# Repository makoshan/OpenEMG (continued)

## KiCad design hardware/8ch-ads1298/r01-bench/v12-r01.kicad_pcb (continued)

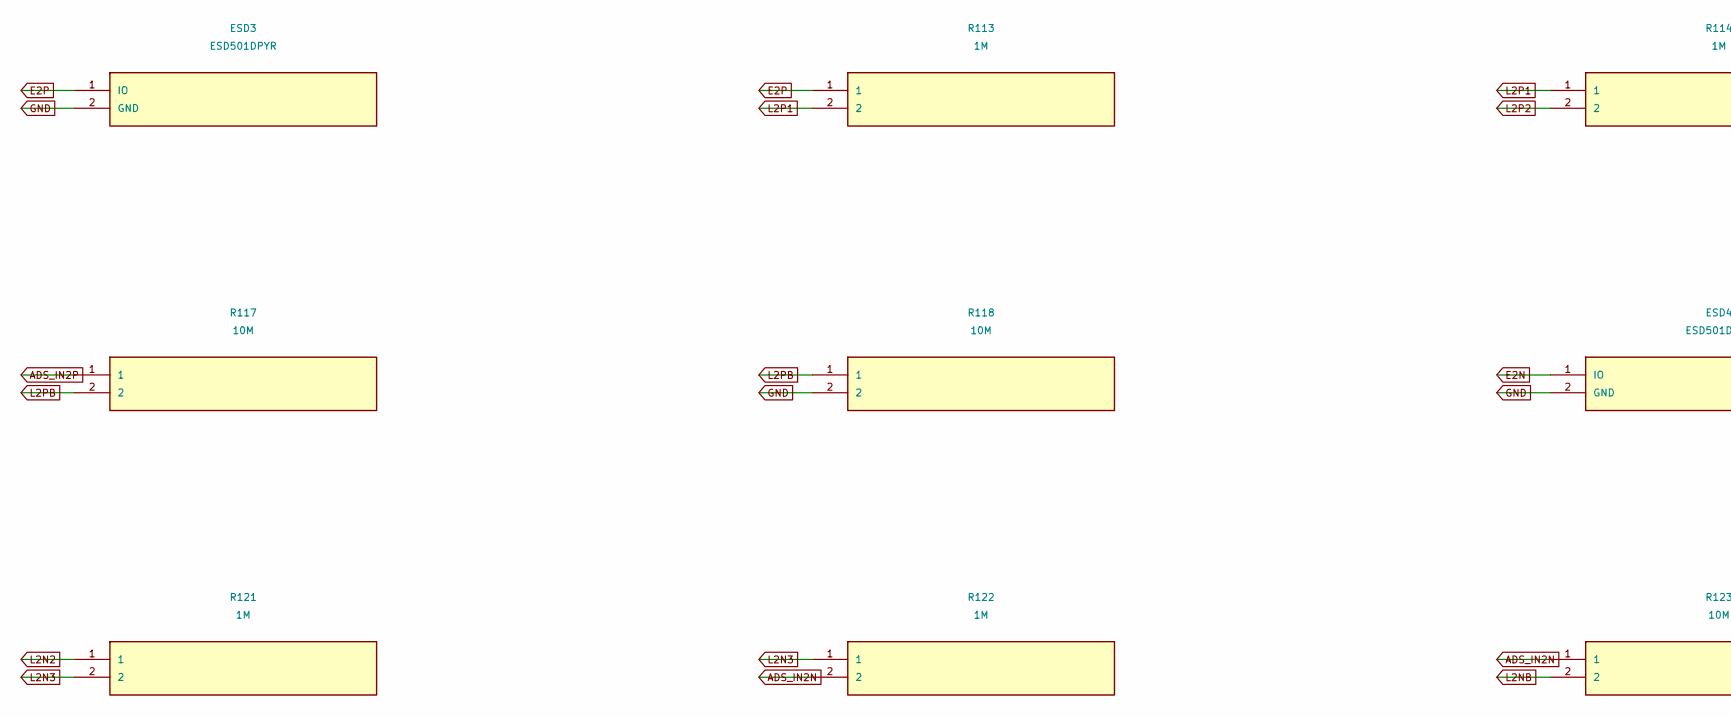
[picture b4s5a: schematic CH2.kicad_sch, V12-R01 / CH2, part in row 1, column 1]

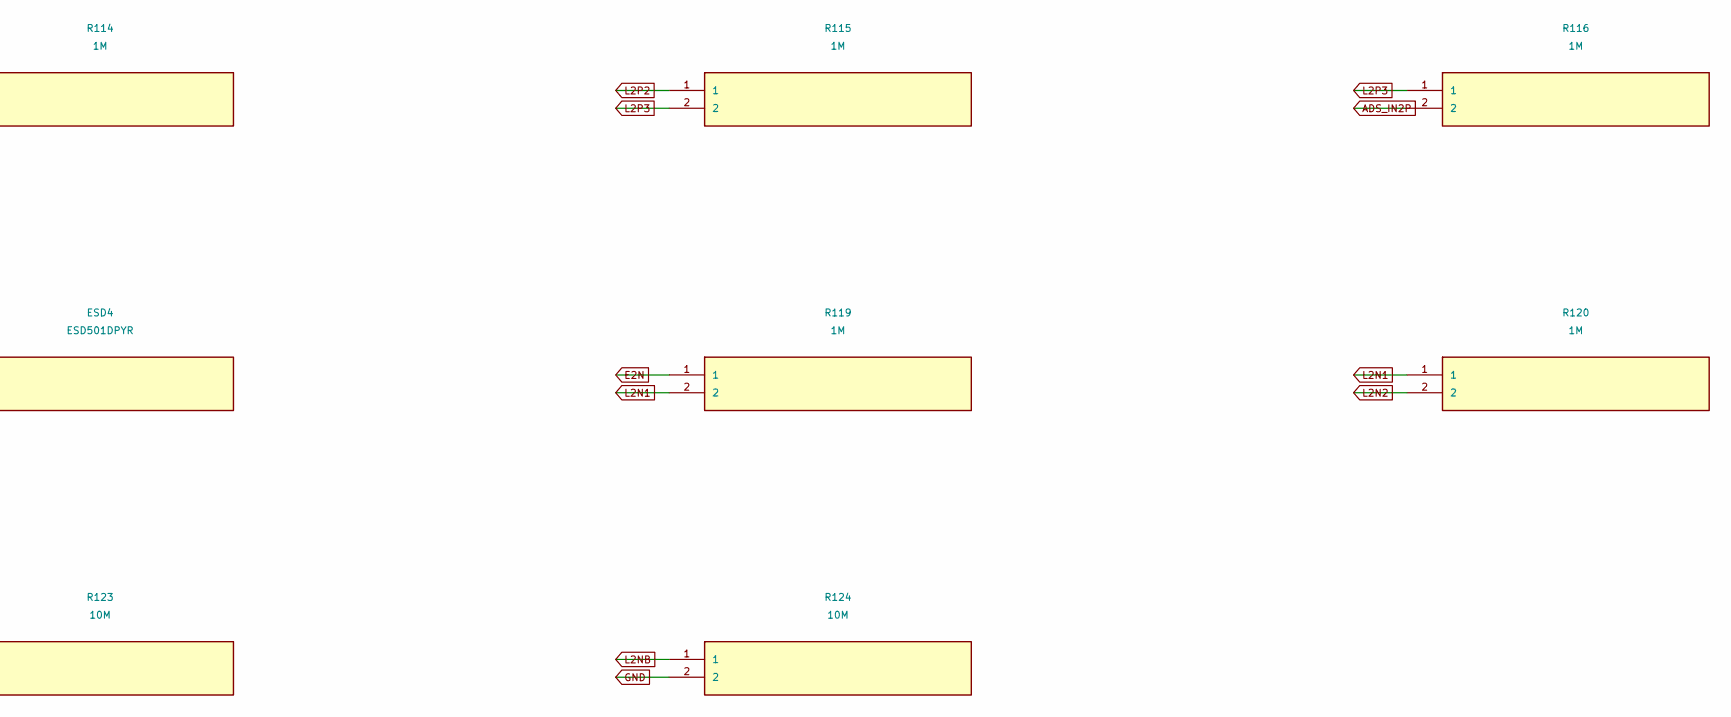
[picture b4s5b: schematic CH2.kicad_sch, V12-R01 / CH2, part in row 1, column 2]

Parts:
ESD3, ESD4: ESD501DPYR; Texas_DPY0002A_0.6x1mm_P0.65mm
R113, R114, R115, R116, R119, R120, R121, R122: 1M; R_0402_1005Metric
R117, R118, R123, R124: 10M; R_0402_1005Metric

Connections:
ADS_IN2N: R122.2, R123.1; also elsewhere on the board
ADS_IN2P: R116.2, R117.1; also elsewhere on the board
E2N: ESD4.1 (IO), R119.1; also elsewhere on the board
E2P: ESD3.1 (IO), R113.1; also elsewhere on the board
GND: ESD3.2 (GND), ESD4.2 (GND), R118.2, R124.2; also elsewhere on the board
L2N1: R119.2, R120.1
L2N2: R120.2, R121.1
L2N3: R121.2, R122.1
L2NB: R123.2, R124.1
L2P1: R113.2, R114.1
L2P2: R114.2, R115.1
L2P3: R115.2, R116.1
L2PB: R117.2, R118.1

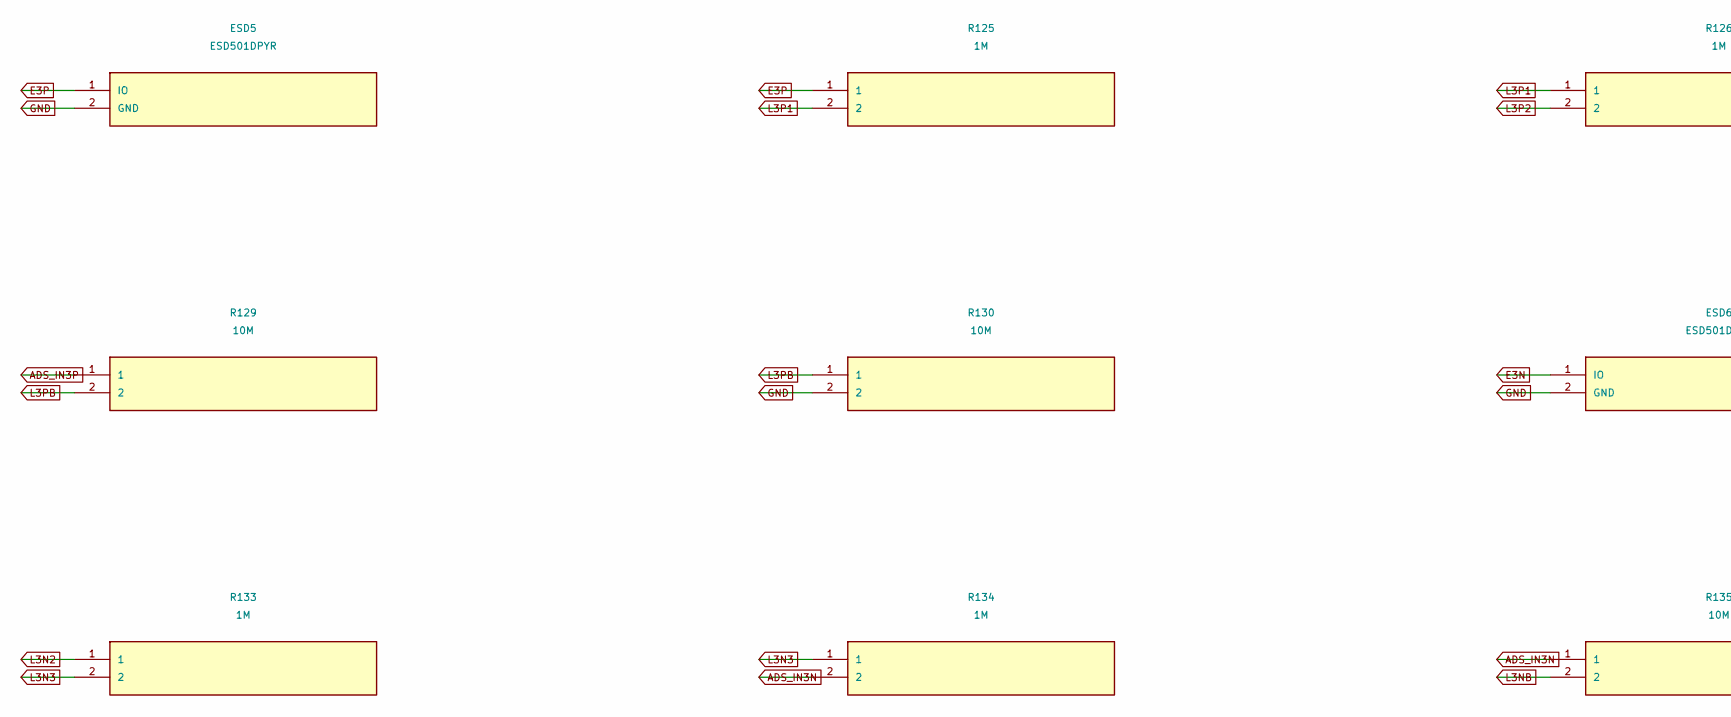
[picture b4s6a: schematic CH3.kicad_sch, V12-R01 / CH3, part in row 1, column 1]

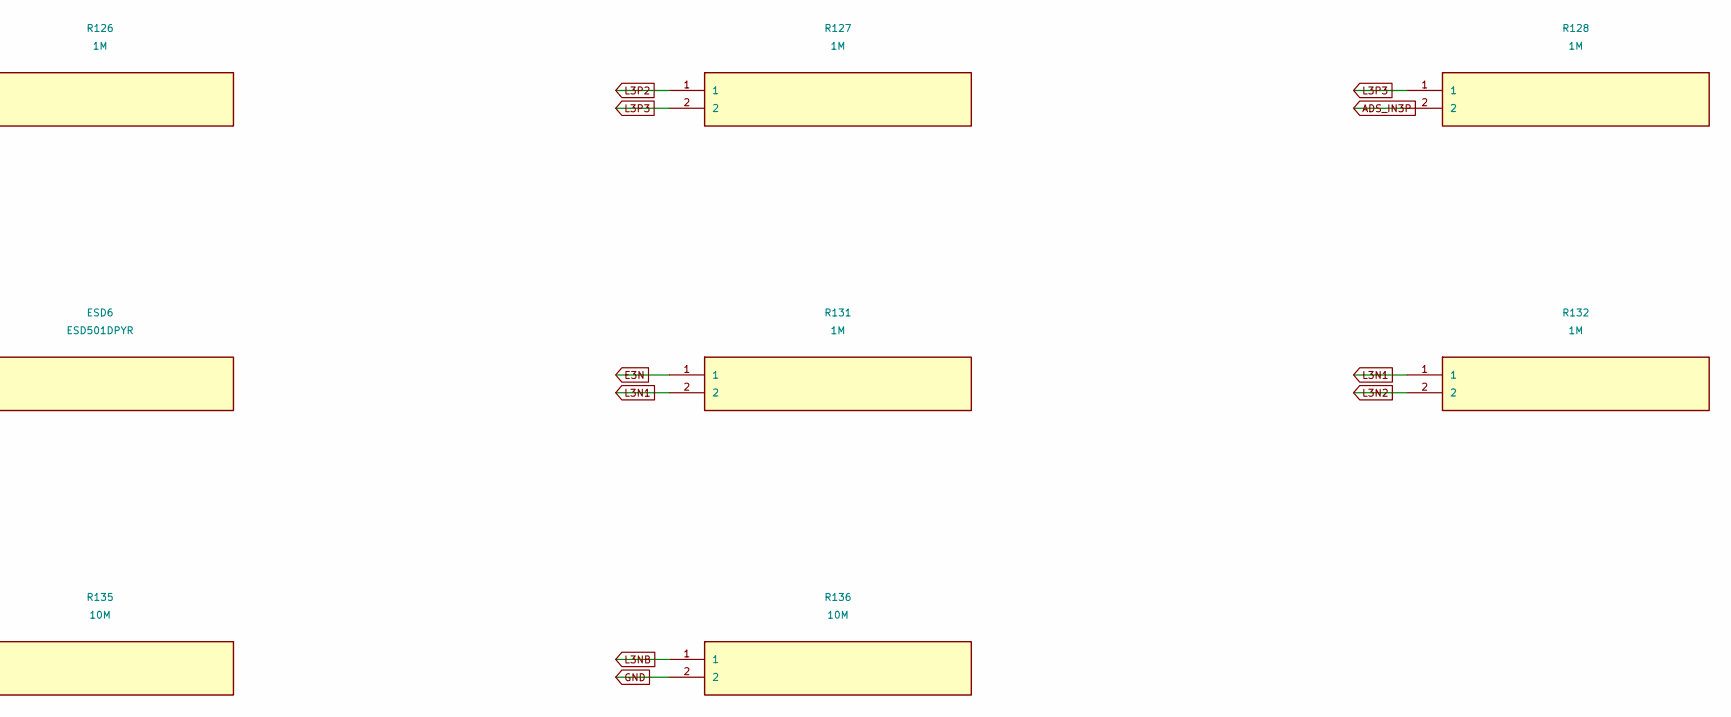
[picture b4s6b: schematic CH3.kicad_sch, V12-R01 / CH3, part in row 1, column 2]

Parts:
ESD5, ESD6: ESD501DPYR; Texas_DPY0002A_0.6x1mm_P0.65mm
R125, R126, R127, R128, R131, R132, R133, R134: 1M; R_0402_1005Metric
R129, R130, R135, R136: 10M; R_0402_1005Metric

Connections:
ADS_IN3N: R134.2, R135.1; also elsewhere on the board
ADS_IN3P: R128.2, R129.1; also elsewhere on the board
E3N: ESD6.1 (IO), R131.1; also elsewhere on the board
E3P: ESD5.1 (IO), R125.1; also elsewhere on the board
GND: ESD5.2 (GND), ESD6.2 (GND), R130.2, R136.2; also elsewhere on the board
L3N1: R131.2, R132.1
L3N2: R132.2, R133.1
L3N3: R133.2, R134.1
L3NB: R135.2, R136.1
L3P1: R125.2, R126.1
L3P2: R126.2, R127.1
L3P3: R127.2, R128.1
L3PB: R129.2, R130.1

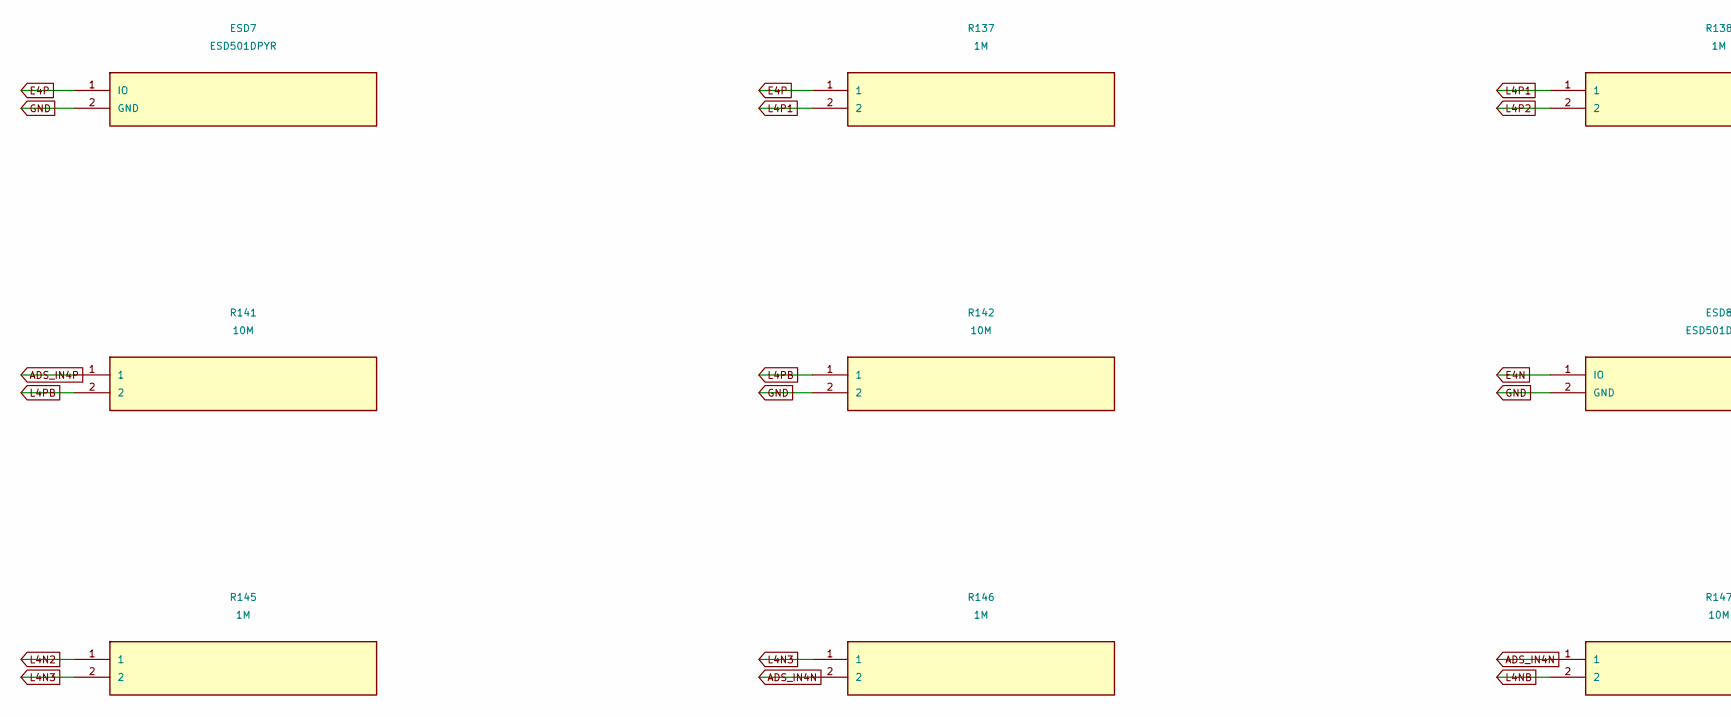
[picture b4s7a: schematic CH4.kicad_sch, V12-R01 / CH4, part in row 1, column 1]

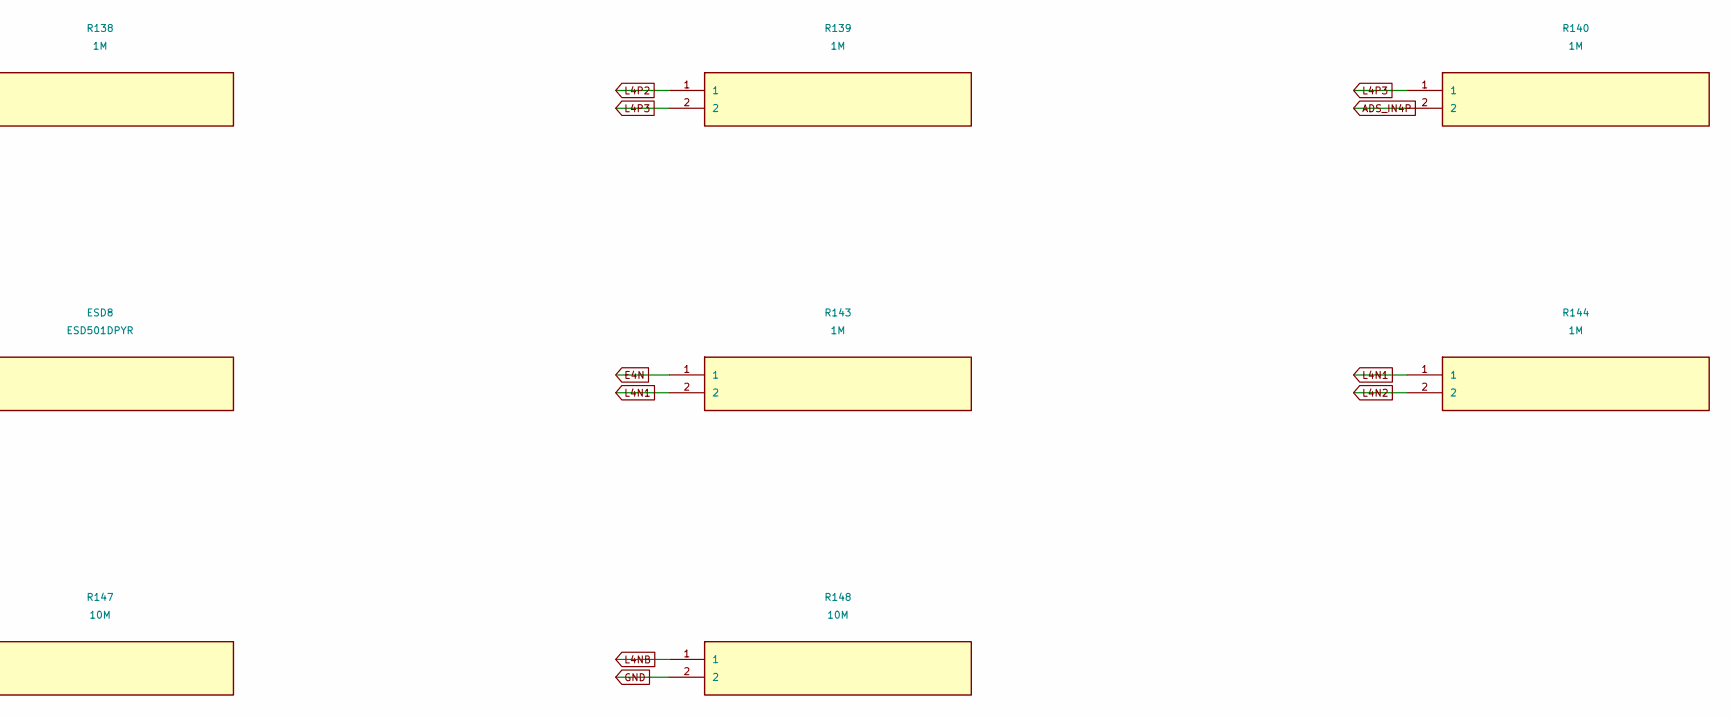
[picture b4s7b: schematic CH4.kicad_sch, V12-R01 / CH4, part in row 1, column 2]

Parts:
ESD7, ESD8: ESD501DPYR; Texas_DPY0002A_0.6x1mm_P0.65mm
R137, R138, R139, R140, R143, R144, R145, R146: 1M; R_0402_1005Metric
R141, R142, R147, R148: 10M; R_0402_1005Metric

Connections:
ADS_IN4N: R146.2, R147.1; also elsewhere on the board
ADS_IN4P: R140.2, R141.1; also elsewhere on the board
E4N: ESD8.1 (IO), R143.1; also elsewhere on the board
E4P: ESD7.1 (IO), R137.1; also elsewhere on the board
GND: ESD7.2 (GND), ESD8.2 (GND), R142.2, R148.2; also elsewhere on the board
L4N1: R143.2, R144.1
L4N2: R144.2, R145.1
L4N3: R145.2, R146.1
L4NB: R147.2, R148.1
L4P1: R137.2, R138.1
L4P2: R138.2, R139.1
L4P3: R139.2, R140.1
L4PB: R141.2, R142.1

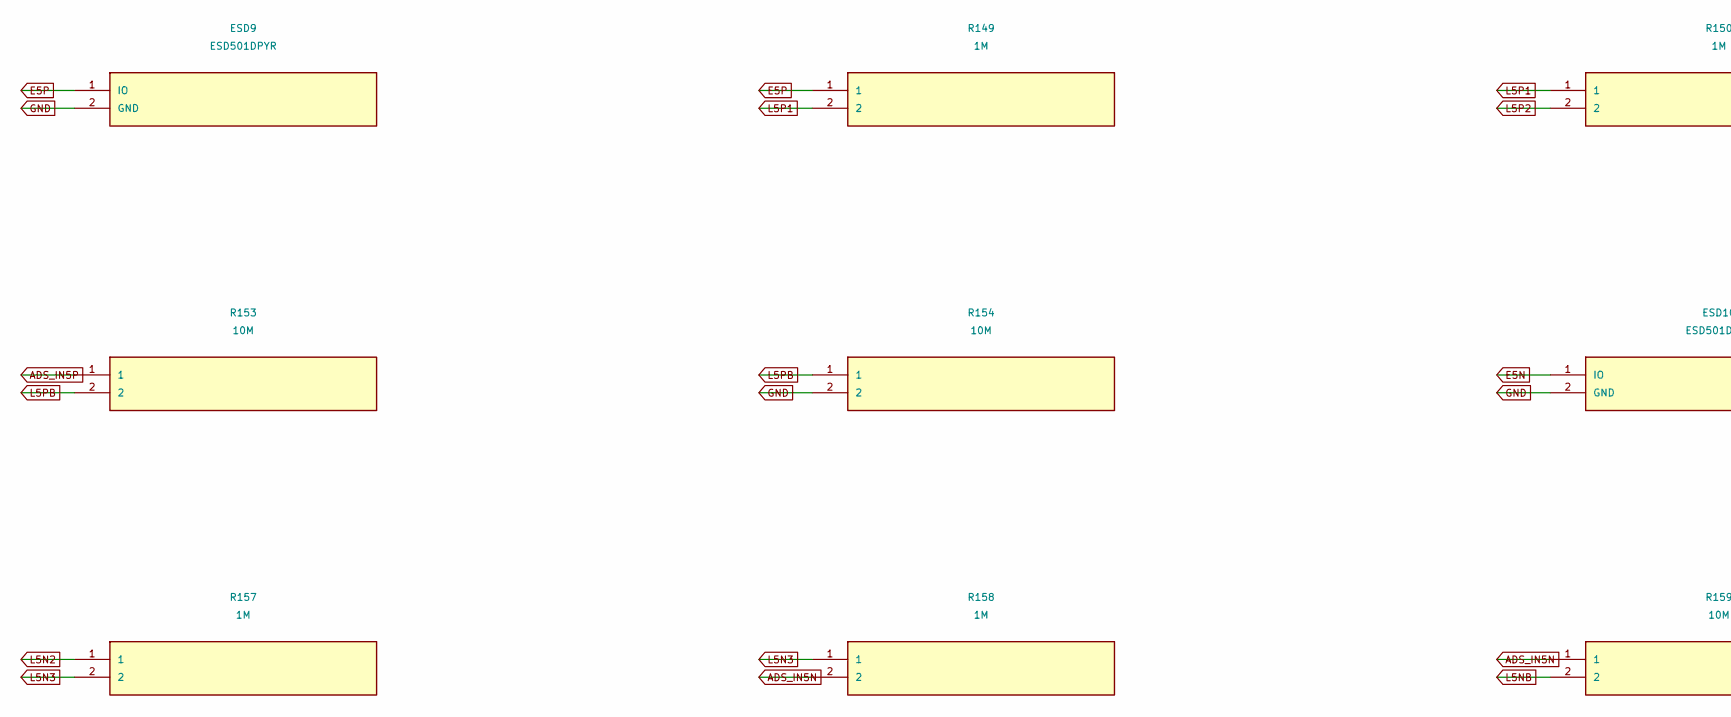
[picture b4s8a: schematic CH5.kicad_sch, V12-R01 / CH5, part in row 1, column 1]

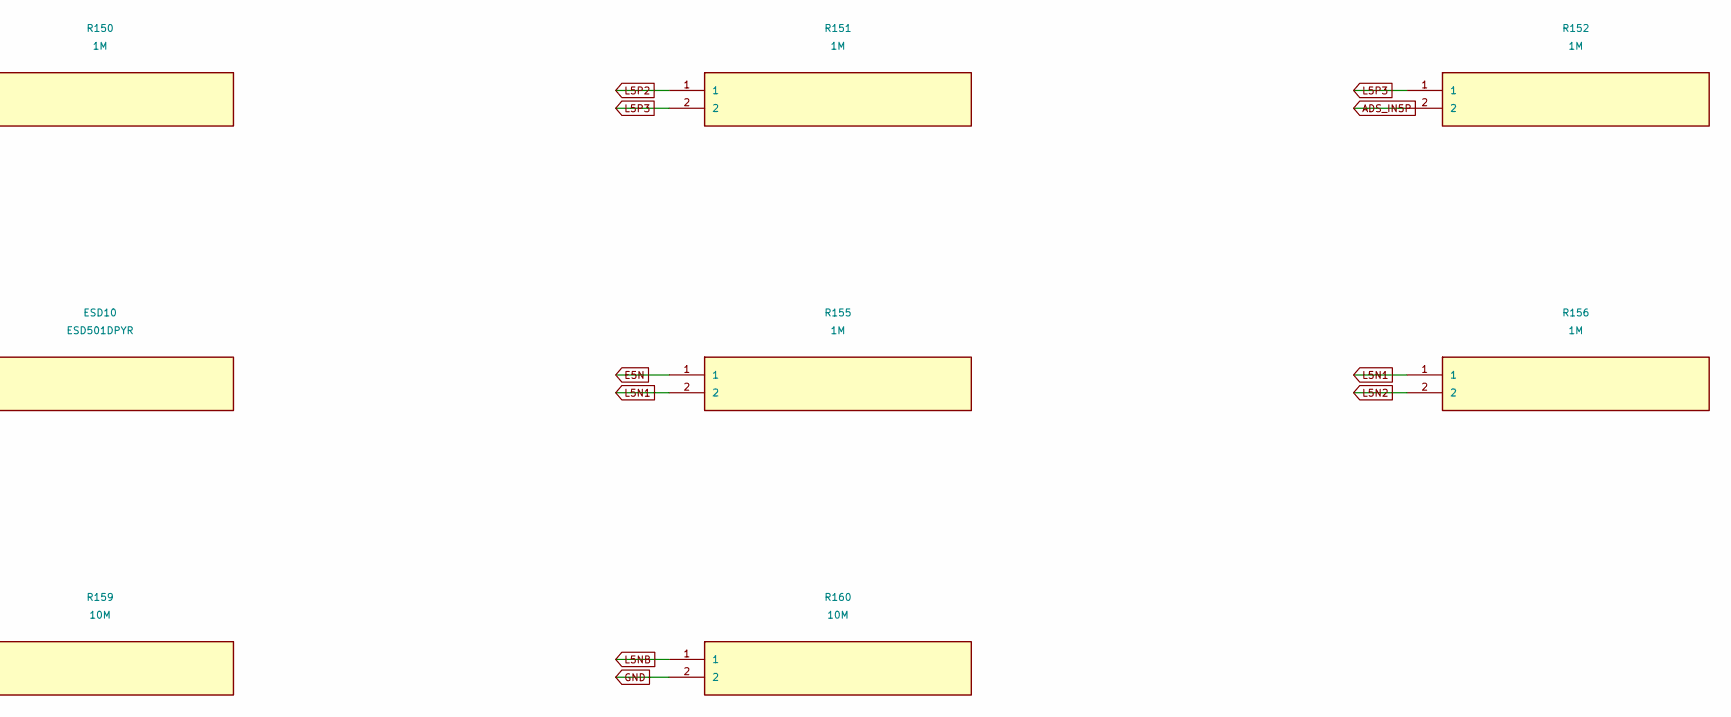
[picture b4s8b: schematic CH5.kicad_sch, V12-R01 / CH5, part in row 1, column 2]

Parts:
ESD9, ESD10: ESD501DPYR; Texas_DPY0002A_0.6x1mm_P0.65mm
R149, R150, R151, R152, R155, R156, R157, R158: 1M; R_0402_1005Metric
R153, R154, R159, R160: 10M; R_0402_1005Metric

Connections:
ADS_IN5N: R158.2, R159.1; also elsewhere on the board
ADS_IN5P: R152.2, R153.1; also elsewhere on the board
E5N: ESD10.1 (IO), R155.1; also elsewhere on the board
E5P: ESD9.1 (IO), R149.1; also elsewhere on the board
GND: ESD9.2 (GND), ESD10.2 (GND), R154.2, R160.2; also elsewhere on the board
L5N1: R155.2, R156.1
L5N2: R156.2, R157.1
L5N3: R157.2, R158.1
L5NB: R159.2, R160.1
L5P1: R149.2, R150.1
L5P2: R150.2, R151.1
L5P3: R151.2, R152.1
L5PB: R153.2, R154.1

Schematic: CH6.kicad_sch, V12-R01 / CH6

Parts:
ESD11, ESD12: ESD501DPYR; Texas_DPY0002A_0.6x1mm_P0.65mm
R161, R162, R163, R164, R167, R168, R169, R170: 1M; R_0402_1005Metric
R165, R166, R171, R172: 10M; R_0402_1005Metric

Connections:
ADS_IN6N: R170.2, R171.1; also elsewhere on the board
ADS_IN6P: R164.2, R165.1; also elsewhere on the board
E6N: ESD12.1 (IO), R167.1; also elsewhere on the board
E6P: ESD11.1 (IO), R161.1; also elsewhere on the board
GND: ESD11.2 (GND), ESD12.2 (GND), R166.2, R172.2; also elsewhere on the board
L6N1: R167.2, R168.1
L6N2: R168.2, R169.1
L6N3: R169.2, R170.1
L6NB: R171.2, R172.1
L6P1: R161.2, R162.1
L6P2: R162.2, R163.1
L6P3: R163.2, R164.1
L6PB: R165.2, R166.1

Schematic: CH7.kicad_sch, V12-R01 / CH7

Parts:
ESD13, ESD14: ESD501DPYR; Texas_DPY0002A_0.6x1mm_P0.65mm
R173, R174, R175, R176, R179, R180, R181, R182: 1M; R_0402_1005Metric
R177, R178, R183, R184: 10M; R_0402_1005Metric

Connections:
ADS_IN7N: R182.2, R183.1; also elsewhere on the board
ADS_IN7P: R176.2, R177.1; also elsewhere on the board
E7N: ESD14.1 (IO), R179.1; also elsewhere on the board
E7P: ESD13.1 (IO), R173.1; also elsewhere on the board
GND: ESD13.2 (GND), ESD14.2 (GND), R178.2, R184.2; also elsewhere on the board
L7N1: R179.2, R180.1
L7N2: R180.2, R181.1
L7N3: R181.2, R182.1
L7NB: R183.2, R184.1
L7P1: R173.2, R174.1
L7P2: R174.2, R175.1
L7P3: R175.2, R176.1
L7PB: R177.2, R178.1

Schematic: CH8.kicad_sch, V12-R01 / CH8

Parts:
ESD15, ESD16: ESD501DPYR; Texas_DPY0002A_0.6x1mm_P0.65mm
R185, R186, R187, R188, R191, R192, R193, R194: 1M; R_0402_1005Metric
R189, R190, R195, R196: 10M; R_0402_1005Metric

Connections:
ADS_IN8N: R194.2, R195.1; also elsewhere on the board
ADS_IN8P: R188.2, R189.1; also elsewhere on the board
E8N: ESD16.1 (IO), R191.1; also elsewhere on the board
E8P: ESD15.1 (IO), R185.1; also elsewhere on the board
GND: ESD15.2 (GND), ESD16.2 (GND), R190.2, R196.2; also elsewhere on the board
L8N1: R191.2, R192.1
L8N2: R192.2, R193.1
L8N3: R193.2, R194.1
L8NB: R195.2, R196.1
L8P1: R185.2, R186.1
L8P2: R186.2, R187.1
L8P3: R187.2, R188.1
L8PB: R189.2, R190.1

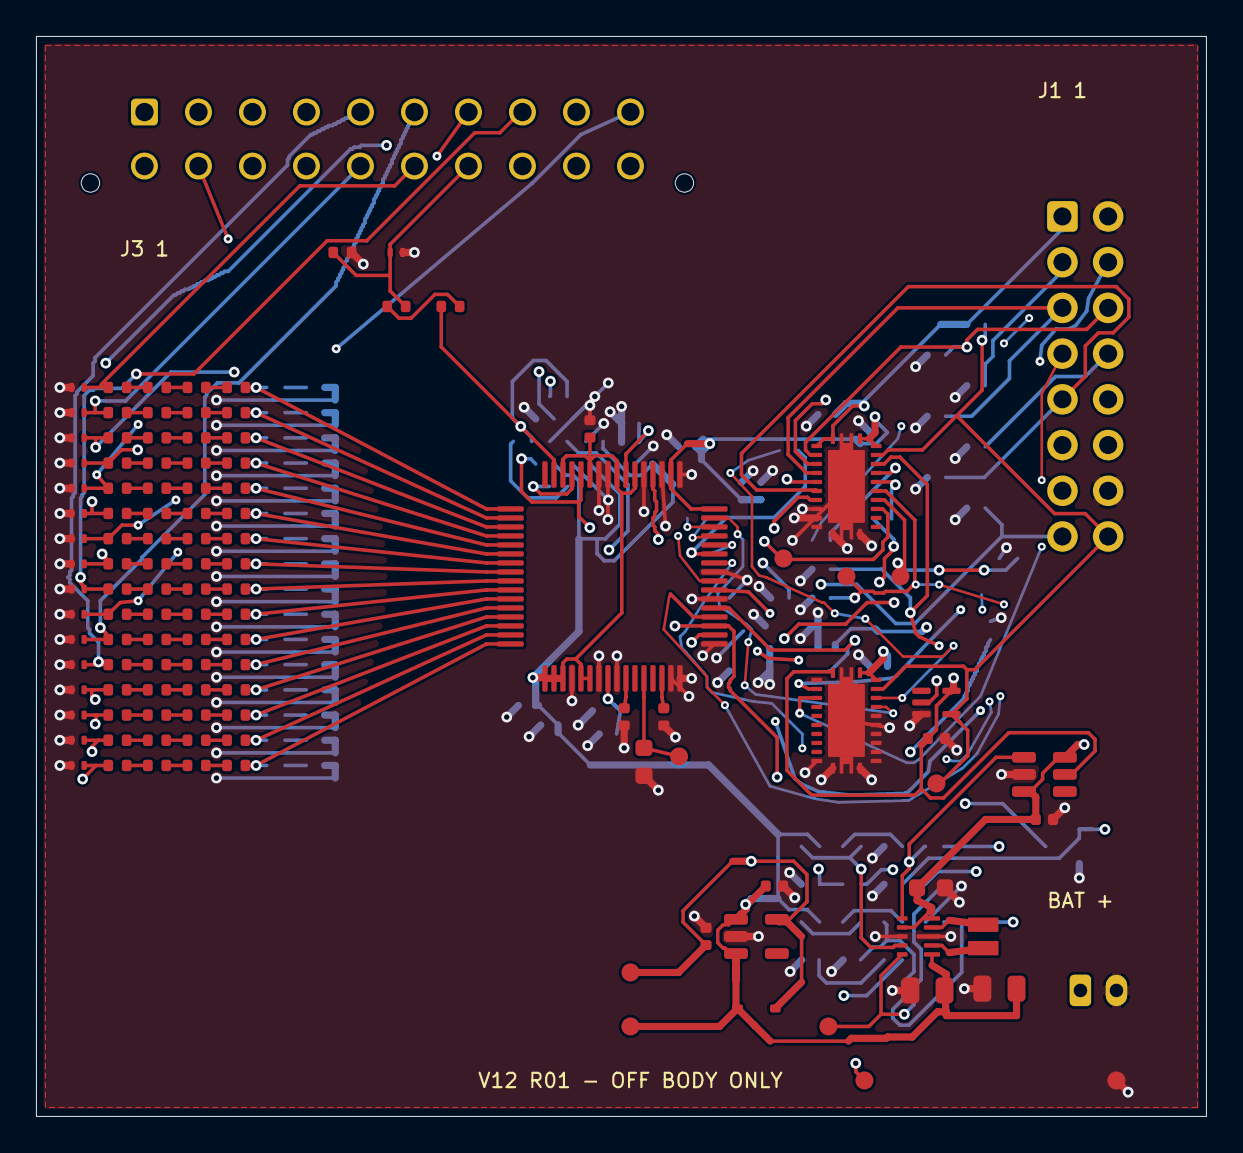
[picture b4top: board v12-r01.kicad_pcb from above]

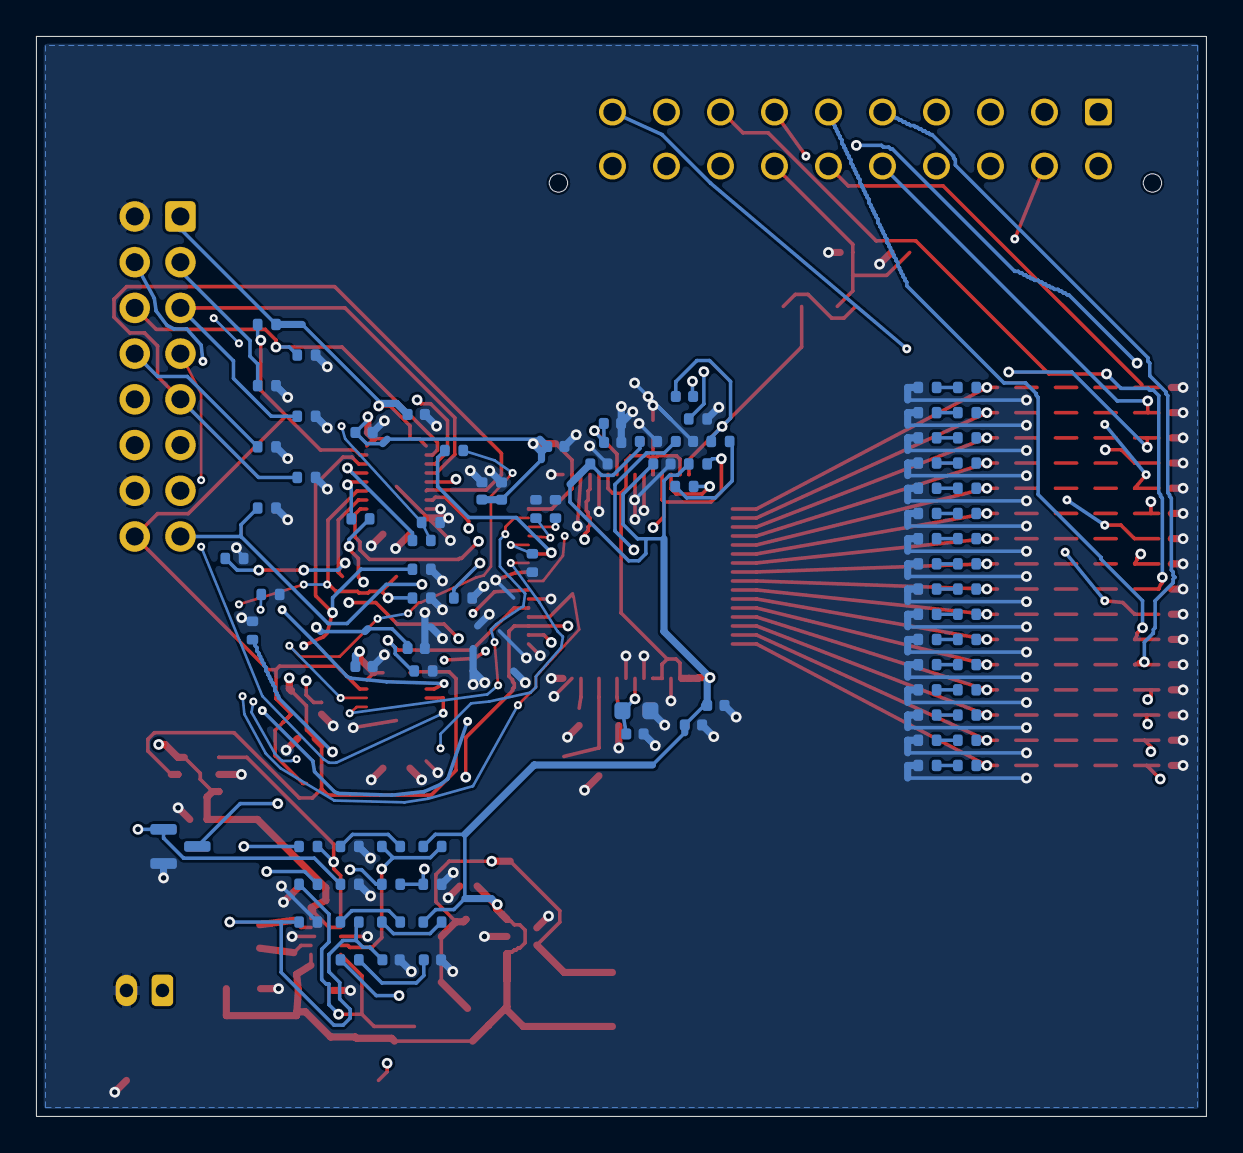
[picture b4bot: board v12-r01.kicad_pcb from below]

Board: 4 copper layers, 65.0 x 60.0 mm, 208 parts (91 on the bottom side), 150 nets.

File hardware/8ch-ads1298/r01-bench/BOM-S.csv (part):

Reference,Value,LCSC,Footprint,Variant,Note
U1,ADS1298IPAGR,C527440,Package_QFP:TQFP-64_10x10mm_P0.5mm,S,RLDIN未用接AVDD；固件必须禁止RLD_MEAS及CHnSET的RLDIN路由。
C1,10uF,C19702,Capacitor_SMD:C_0603_1608Metric,S,
C2,1uF,C52923,Capacitor_SMD:C_0402_1005Metric,S,
C3,22uF,C59461,Capacitor_SMD:C_0603_1608Metric,S,有效电容/压电噪声待核
C4,1uF,C52923,Capacitor_SMD:C_0402_1005Metric,S,
C5,1uF,C52923,Capacitor_SMD:C_0402_1005Metric,S,
C6,100nF,C1525,Capacitor_SMD:C_0402_1005Metric,S,
C7,1uF,C52923,Capacitor_SMD:C_0402_1005Metric,S,
C8,1uF,C52923,Capacitor_SMD:C_0402_1005Metric,S,AVDD 脚 19/21/22
C9,100nF,C1525,Capacitor_SMD:C_0402_1005Metric,S,AVDD 脚 19/21/22
C10,1uF,C52923,Capacitor_SMD:C_0402_1005Metric,S,AVDD 脚 54 AVDD1
C11,100nF,C1525,Capacitor_SMD:C_0402_1005Metric,S,AVDD 脚 54 AVDD1
C12,1uF,C52923,Capacitor_SMD:C_0402_1005Metric,S,AVDD 脚 56/59
C13,100nF,C1525,Capacitor_SMD:C_0402_1005Metric,S,AVDD 脚 56/59
C14,100nF,C1525,Capacitor_SMD:C_0402_1005Metric,S,DVDD 脚 48
C15,100nF,C1525,Capacitor_SMD:C_0402_1005Metric,S,DVDD 脚 50
C16,1uF,C52923,Capacitor_SMD:C_0402_1005Metric,S,
R1,100k,C25741,Resistor_SMD:R_0402_1005Metric,S,
R2,100k,C25741,Resistor_SMD:R_0402_1005Metric,S,
C17,1uF,C52923,Capacitor_SMD:C_0402_1005Metric,S,
R3,200k,C25764,Resistor_SMD:R_0402_1005Metric,S,
R4,200k,C25764,Resistor_SMD:R_0402_1005Metric,S,
C18,10nF,C15195,Capacitor_SMD:C_0402_1005Metric,S,
R5,200k,C25764,Resistor_SMD:R_0402_1005Metric,S,
R6,200k,C25764,Resistor_SMD:R_0402_1005Metric,S,
R7,10M,C2933065,Resistor_SMD:R_0402_1005Metric,S,
ESD17,ESD501DPYR,C42409135,Package_SON:Texas_DPY0002A_0.6x1mm_P0.65mm,S,
R8,33R,C25105,Resistor_SMD:R_0402_1005Metric,S,
R9,33R,C25105,Resistor_SMD:R_0402_1005Metric,S,
R10,33R,C25105,Resistor_SMD:R_0402_1005Metric,S,
R11,10k,C25744,Resistor_SMD:R_0402_1005Metric,S,
R12,10k,C25744,Resistor_SMD:R_0402_1005Metric,S,
R13,10k,C25744,Resistor_SMD:R_0402_1005Metric,S,
R14,10k,C25744,Resistor_SMD:R_0402_1005Metric,S,
R15,10k,C25744,Resistor_SMD:R_0402_1005Metric,S,
R16,10k,C25744,Resistor_SMD:R_0402_1005Metric,S,
R17,10k,C25744,Resistor_SMD:R_0402_1005Metric,S,
R18,10k,C25744,Resistor_SMD:R_0402_1005Metric,S,
R19,10k,C25744,Resistor_SMD:R_0402_1005Metric,S,
R20,10k,C25744,Resistor_SMD:R_0402_1005Metric,S,
ESD1,ESD501DPYR,C42409135,Package_SON:Texas_DPY0002A_0.6x1mm_P0.65mm,S,
R101,1M,C26083,Resistor_SMD:R_0402_1005Metric,S,
R102,1M,C26083,Resistor_SMD:R_0402_1005Metric,S,
R103,1M,C26083,Resistor_SMD:R_0402_1005Metric,S,
R104,1M,C26083,Resistor_SMD:R_0402_1005Metric,S,
R105,10M,C2933065,Resistor_SMD:R_0402_1005Metric,S,
R106,10M,C2933065,Resistor_SMD:R_0402_1005Metric,S,
ESD2,ESD501DPYR,C42409135,Package_SON:Texas_DPY0002A_0.6x1mm_P0.65mm,S,
R107,1M,C26083,Resistor_SMD:R_0402_1005Metric,S,
R108,1M,C26083,Resistor_SMD:R_0402_1005Metric,S,
R109,1M,C26083,Resistor_SMD:R_0402_1005Metric,S,
R110,1M,C26083,Resistor_SMD:R_0402_1005Metric,S,
R111,10M,C2933065,Resistor_SMD:R_0402_1005Metric,S,
R112,10M,C2933065,Resistor_SMD:R_0402_1005Metric,S,
ESD3,ESD501DPYR,C42409135,Package_SON:Texas_DPY0002A_0.6x1mm_P0.65mm,S,
R113,1M,C26083,Resistor_SMD:R_0402_1005Metric,S,
R114,1M,C26083,Resistor_SMD:R_0402_1005Metric,S,
R115,1M,C26083,Resistor_SMD:R_0402_1005Metric,S,
R116,1M,C26083,Resistor_SMD:R_0402_1005Metric,S,
R117,10M,C2933065,Resistor_SMD:R_0402_1005Metric,S,
R118,10M,C2933065,Resistor_SMD:R_0402_1005Metric,S,
ESD4,ESD501DPYR,C42409135,Package_SON:Texas_DPY0002A_0.6x1mm_P0.65mm,S,
R119,1M,C26083,Resistor_SMD:R_0402_1005Metric,S,
R120,1M,C26083,Resistor_SMD:R_0402_1005Metric,S,
R121,1M,C26083,Resistor_SMD:R_0402_1005Metric,S,
R122,1M,C26083,Resistor_SMD:R_0402_1005Metric,S,
R123,10M,C2933065,Resistor_SMD:R_0402_1005Metric,S,
R124,10M,C2933065,Resistor_SMD:R_0402_1005Metric,S,
ESD5,ESD501DPYR,C42409135,Package_SON:Texas_DPY0002A_0.6x1mm_P0.65mm,S,
R125,1M,C26083,Resistor_SMD:R_0402_1005Metric,S,
R126,1M,C26083,Resistor_SMD:R_0402_1005Metric,S,
R127,1M,C26083,Resistor_SMD:R_0402_1005Metric,S,
R128,1M,C26083,Resistor_SMD:R_0402_1005Metric,S,
R129,10M,C2933065,Resistor_SMD:R_0402_1005Metric,S,
R130,10M,C2933065,Resistor_SMD:R_0402_1005Metric,S,
ESD6,ESD501DPYR,C42409135,Package_SON:Texas_DPY0002A_0.6x1mm_P0.65mm,S,
R131,1M,C26083,Resistor_SMD:R_0402_1005Metric,S,
R132,1M,C26083,Resistor_SMD:R_0402_1005Metric,S,
R133,1M,C26083,Resistor_SMD:R_0402_1005Metric,S,
R134,1M,C26083,Resistor_SMD:R_0402_1005Metric,S,
R135,10M,C2933065,Resistor_SMD:R_0402_1005Metric,S,
R136,10M,C2933065,Resistor_SMD:R_0402_1005Metric,S,
ESD7,ESD501DPYR,C42409135,Package_SON:Texas_DPY0002A_0.6x1mm_P0.65mm,S,
R137,1M,C26083,Resistor_SMD:R_0402_1005Metric,S,
R138,1M,C26083,Resistor_SMD:R_0402_1005Metric,S,
R139,1M,C26083,Resistor_SMD:R_0402_1005Metric,S,
R140,1M,C26083,Resistor_SMD:R_0402_1005Metric,S,
R141,10M,C2933065,Resistor_SMD:R_0402_1005Metric,S,
R142,10M,C2933065,Resistor_SMD:R_0402_1005Metric,S,
ESD8,ESD501DPYR,C42409135,Package_SON:Texas_DPY0002A_0.6x1mm_P0.65mm,S,
R143,1M,C26083,Resistor_SMD:R_0402_1005Metric,S,
R144,1M,C26083,Resistor_SMD:R_0402_1005Metric,S,
R145,1M,C26083,Resistor_SMD:R_0402_1005Metric,S,
R146,1M,C26083,Resistor_SMD:R_0402_1005Metric,S,
R147,10M,C2933065,Resistor_SMD:R_0402_1005Metric,S,
R148,10M,C2933065,Resistor_SMD:R_0402_1005Metric,S,
ESD9,ESD501DPYR,C42409135,Package_SON:Texas_DPY0002A_0.6x1mm_P0.65mm,S,
R149,1M,C26083,Resistor_SMD:R_0402_1005Metric,S,
R150,1M,C26083,Resistor_SMD:R_0402_1005Metric,S,
R151,1M,C26083,Resistor_SMD:R_0402_1005Metric,S,
R152,1M,C26083,Resistor_SMD:R_0402_1005Metric,S,
R153,10M,C2933065,Resistor_SMD:R_0402_1005Metric,S,
R154,10M,C2933065,Resistor_SMD:R_0402_1005Metric,S,
ESD10,ESD501DPYR,C42409135,Package_SON:Texas_DPY0002A_0.6x1mm_P0.65mm,S,
R155,1M,C26083,Resistor_SMD:R_0402_1005Metric,S,
R156,1M,C26083,Resistor_SMD:R_0402_1005Metric,S,
R157,1M,C26083,Resistor_SMD:R_0402_1005Metric,S,
R158,1M,C26083,Resistor_SMD:R_0402_1005Metric,S,
R159,10M,C2933065,Resistor_SMD:R_0402_1005Metric,S,
R160,10M,C2933065,Resistor_SMD:R_0402_1005Metric,S,
ESD11,ESD501DPYR,C42409135,Package_SON:Texas_DPY0002A_0.6x1mm_P0.65mm,S,
R161,1M,C26083,Resistor_SMD:R_0402_1005Metric,S,
R162,1M,C26083,Resistor_SMD:R_0402_1005Metric,S,
R163,1M,C26083,Resistor_SMD:R_0402_1005Metric,S,
R164,1M,C26083,Resistor_SMD:R_0402_1005Metric,S,
R165,10M,C2933065,Resistor_SMD:R_0402_1005Metric,S,
R166,10M,C2933065,Resistor_SMD:R_0402_1005Metric,S,
ESD12,ESD501DPYR,C42409135,Package_SON:Texas_DPY0002A_0.6x1mm_P0.65mm,S,
R167,1M,C26083,Resistor_SMD:R_0402_1005Metric,S,
R168,1M,C26083,Resistor_SMD:R_0402_1005Metric,S,
R169,1M,C26083,Resistor_SMD:R_0402_1005Metric,S,
R170,1M,C26083,Resistor_SMD:R_0402_1005Metric,S,
R171,10M,C2933065,Resistor_SMD:R_0402_1005Metric,S,
R172,10M,C2933065,Resistor_SMD:R_0402_1005Metric,S,
ESD13,ESD501DPYR,C42409135,Package_SON:Texas_DPY0002A_0.6x1mm_P0.65mm,S,
R173,1M,C26083,Resistor_SMD:R_0402_1005Metric,S,
R174,1M,C26083,Resistor_SMD:R_0402_1005Metric,S,
R175,1M,C26083,Resistor_SMD:R_0402_1005Metric,S,
R176,1M,C26083,Resistor_SMD:R_0402_1005Metric,S,
R177,10M,C2933065,Resistor_SMD:R_0402_1005Metric,S,
R178,10M,C2933065,Resistor_SMD:R_0402_1005Metric,S,
ESD14,ESD501DPYR,C42409135,Package_SON:Texas_DPY0002A_0.6x1mm_P0.65mm,S,
R179,1M,C26083,Resistor_SMD:R_0402_1005Metric,S,
R180,1M,C26083,Resistor_SMD:R_0402_1005Metric,S,
R181,1M,C26083,Resistor_SMD:R_0402_1005Metric,S,
R182,1M,C26083,Resistor_SMD:R_0402_1005Metric,S,
R183,10M,C2933065,Resistor_SMD:R_0402_1005Metric,S,
R184,10M,C2933065,Resistor_SMD:R_0402_1005Metric,S,
ESD15,ESD501DPYR,C42409135,Package_SON:Texas_DPY0002A_0.6x1mm_P0.65mm,S,
R185,1M,C26083,Resistor_SMD:R_0402_1005Metric,S,
R186,1M,C26083,Resistor_SMD:R_0402_1005Metric,S,
R187,1M,C26083,Resistor_SMD:R_0402_1005Metric,S,
R188,1M,C26083,Resistor_SMD:R_0402_1005Metric,S,
R189,10M,C2933065,Resistor_SMD:R_0402_1005Metric,S,
R190,10M,C2933065,Resistor_SMD:R_0402_1005Metric,S,
ESD16,ESD501DPYR,C42409135,Package_SON:Texas_DPY0002A_0.6x1mm_P0.65mm,S,
R191,1M,C26083,Resistor_SMD:R_0402_1005Metric,S,
R192,1M,C26083,Resistor_SMD:R_0402_1005Metric,S,
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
